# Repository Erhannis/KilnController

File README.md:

Kiln controller PCB, in KiCAD.  ESP32, controlled (potentially) over wifi.

# Instructions 
Comes with two thermocouple readers and controls three heating elements.  Attach thermocouples to appropriate points, attach three SSR-DA60 to HEAT1-HEAT3 and another to ALL_POWER, wire in 240V (see instructions on board), recommended don't attach USB while mains voltage is connected; the 5V sources might conflict - also just seems a little unsafe.  The board is shaped to match my Everheat Classic 1210 frontplate - hopefully it fits, haha.  You can reshape it if you want, or just run wires to your thermocouples and elements.  The Main TC is for inside the kiln (PIDKiln has a link to a sturdy thermocouple), the Aux TC is for the kiln outside surface (I think it's optional?).  I broke out all 6 unused GPIO pins.  See [code](#code) for firmware.

Warning: if any elements are active, all elements are live at >= 120V.  There's a blue LED that lights up when any element is active; watch out for the blue LED.  ALSO!  I hear that SSRs can fail closed, meaning the elements may stay live even once the blue LED turns off.  So...maybe just unplug the thing if you're gonna touch the coils.

# Code
See my fork of PIDKiln at https://github.com/erhannis/PIDKiln
Note that in order to flash the code, the board must be unpowered to start, you need to connect BOOT to GND, plug the board in via USB, and then you have a handful of seconds to initiate a data transfer at 115200 baud (either the main code flashing, or the "ESP32 Sketch Data Upload").  Try turning on Arduino IDE logs for compilation and upload, then copy the relevant upload command into the terminal, for timing.  Afterward, remove boot jumper and replug the board.

Disclaimer: I have no formal electronics training, and this thing connects to 240V, so like, maybe use this thing away from anything flammable, and on your own head be the results.  And DON'T TOUCH THE COILS WHILE IT'S HEATING!  Because they're live 240V, and also may be hot.

# Additional parts
Thermocouple: https://www.auberins.com/index.php?main_page=product_info&cPath=20_3&products_id=39
  (Also one of the cheap k-type thermocouples from amazon, for the case.  Though, see notes.)
Bus blocks: https://www.amazon.com/dp/B0B2L7QBVN
Heat sinks: https://www.amazon.com/dp/B08ZCYBPTV
SSRs: https://www.amazon.com/dp/B01MSTFKIP (60DA)
  Note that (according to tests) these start and stop conducting at zero volt crossings.  Also, they still let like 2mA through while open, which CAN yield high voltages.
  You might get away with lower amp ones.

# Notes
I picked the slightly more expensive thermocouple readers, which (supposedly) are more accurate and support multiple thermocouple types instead of just K - just in case that turns out to be useful.  If you're not using k-type, though, you'll probably need to tweak something in code to tell the controllers so.
I had trouble where at high temperatures, the readings on both thermocouples would go nuts.  This stopped happening after I hung the case thermocouple away from contact with anything else.  I am baffled as to how that could have happened.

MIT license.

-Erhannis

Btw, I have like 4 extra from the manufacturing batch if anybody want to buy one for like, I dunno, $100, say.  (You'll have to add the SSRs and bus terminals yourself, though.)  Getting 5 boards assembled from JLCPCB costs around $330 total.
(If you're up for soldering the ESP32 WROOM module yourself (difficult), you can use Economy mode instead of Standard and save like $100.)

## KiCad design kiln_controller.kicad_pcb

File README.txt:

Kiln controller PCB, in KiCAD.  ESP32, controlled (potentially) over wifi.

# Instructions
Comes with two thermocouple readers and controls three heating elements.  Attach thermocouples to appropriate points, attach three SSR-DA60 to HEAT1-HEAT3 and another to ALL_POWER, wire in 240V (see instructions on board), recommended don't attach USB while mains voltage is connected; the 5V sources might conflict - also just seems a little unsafe.  The board is shaped to match my Everheat Classic 1210 frontplate - hopefully it fits, haha.  You can reshape it if you want, or just run wires to your thermocouples and elements.  The Main TC is for inside the kiln (PIDKiln has a link to a sturdy thermocouple), the Aux TC is for the kiln outside surface (I think it's optional?).  I broke out all 6 unused GPIO pins.  See [code](#code) for firmware.

Warning: if any elements are active, all elements are live at >= 120V.  There's a blue LED that lights up when any element is active; watch out for the blue LED.  ALSO!  I hear that SSRs can fail closed, meaning the elements may stay live even once the blue LED turns off.  So...maybe just unplug the thing if you're gonna touch the coils.

# Code
See my fork of PIDKiln at https://github.com/erhannis/PIDKiln
Note that in order to flash the code, you need to pull BOOT to GND, plug the board in via USB, and then you have a handful of seconds to initiate a data transfer at 115200 baud (either the main code flashing, or the "ESP32 Sketch Data Upload").  Try turning on Arduino IDE logs for compilation and upload, then copy the relevant upload command into the terminal, for timing.  Afterward, remove boot jumper and replug the board.

Disclaimer: I have no formal electronics training, and this thing connects to 240V, so like, maybe use this thing away from anything flammable, and on your own head be the results.  And DON'T TOUCH THE COILS WHILE IT'S HEATING!  Because they're live 240V, and also may be hot.

# Notes
I picked the slightly more expensive thermocouple readers, which (supposedly) are more accurate and support multiple thermocouple types instead of just K - just in case that turns out to be useful.  If you're not using k-type, though, you'll probably need to tweak something in code to tell the controllers so.

MIT license.

-Erhannis

Btw, I have like 4 extra from the manufacturing batch if anybody want to buy one for like, I dunno, $100, say.  (You'll have to add the SSRs and bus terminals yourself, though.)  Getting 5 boards assembled from JLCPCB costs around $330 total.
(If you're up for soldering the ESP32 WROOM module yourself (difficult), you can use Economy mode instead of Standard and save like $100.)

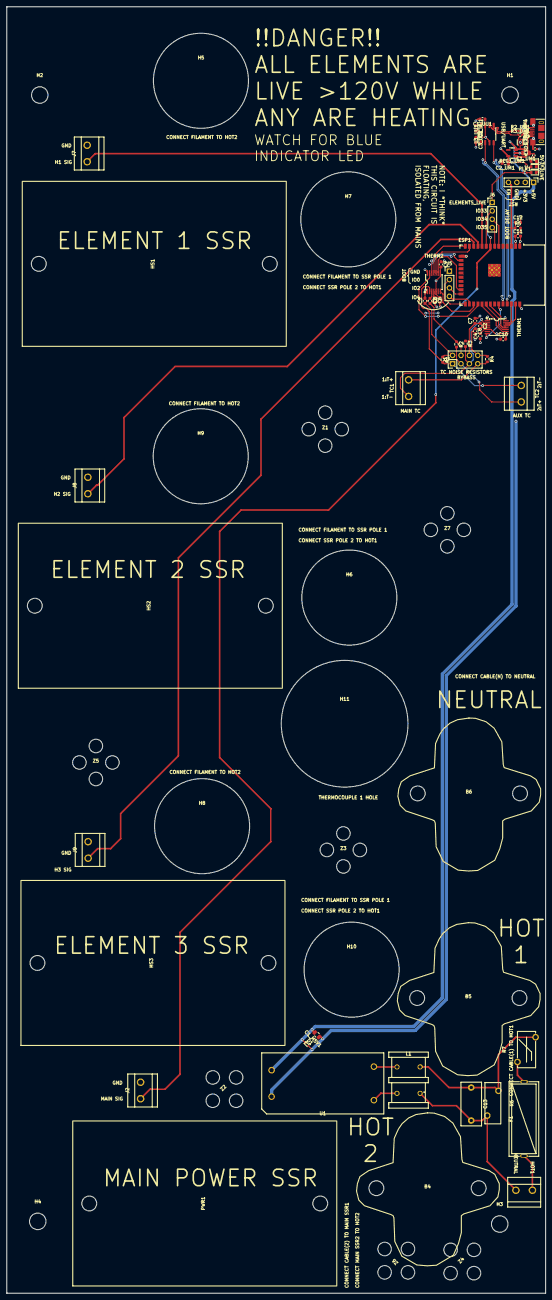
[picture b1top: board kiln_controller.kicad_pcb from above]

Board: 4 copper layers, 163.3 x 389.8 mm, 82 parts (0 on the bottom side), 51 nets.

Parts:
B4, B5, B6: bus_stud
C1, C2, C3, C4, C9, C10: 100nF; C_0603_1608Metric
C1_M5V1, C1_UM1, C2_UM1: 10uF; C_0805_2012Metric
C1_UU1, C2_UU1, C3_UU1, C12: 1uF; C_0603_1608Metric
C5, C6, C7, C8: 10nF; C_0603_1608Metric
C11: 22uF; C_0603_1608Metric
C13: 100nF/275V; C_Rect_L13.0mm_W6.0mm_P10.00mm_FKS3_FKP3_MKS4
D1: ESD9B5.0ST5G; D_SOD-923
D1_UM1: LED(R); LED_0603_1608Metric
D2_UM1: LED(G); LED_0603_1608Metric
ESD1_UM1: USBLC6-2P6; SOT-666
ESP1: ESP32-WROOM-32D
F1: Fuse transparent seat; FUSE-TH_L24.5-W9.8-P22.5
H1, H2, H3, H4: MountingHole; MountingHole_5mm
H5, H6, H7, H8, H9, H10: MountingHole; MountingHole_6mm
H11: MountingHole; MountingHole_6.5mm
HS1, HS2, HS3: SSR Heat Sink
J1: Conn_02x04_Row_Letter_First; PinHeader_2x04_P2.54mm_Vertical
J2, J7, J8, J9, J10: XY126V-5.0-2P; CONN-TH_XY126V-5.0-2P
J4, J5, J6: Conn_01x04_Pin; PinHeader_1x04_P2.54mm_Vertical
L1: UU9.8-20MH; FILTER-TH_4P-L17.0-W12.0-P7.00-D0.6-S8.00
PLED1: LED(B); LED_0603_1608Metric
PLR1: 330; R_0402_1005Metric
PWR1: SSR Heat Sink
R1, R2, R3, R4: 100Ω; R_0603_1608Metric
R1_UM1: 1M; R_0402_1005Metric
R2_UM1, R3_UM1: 27; R_0402_1005Metric
R4_UM1, R5_UM1: 330; R_0402_1005Metric
R5: 10k; R_0603_1608Metric
R6: 471KD10; RES-TH_L12.5-W4.8-P7.50-D1.2-S3.40
R7: 5D-9_C332361; RES-TH_L11.0-W5.5-P7.50-D0.8-S5.50
REG1_UM1: AP2112K-3.3; SOT-23-5
TC1, TC2: XY126V-5.0-2P; CONN-TH_XY126V-5.0-2P
THERM1, THERM2: MAX31856MUD+T; TSSOP-14_L5.0-W4.4-P0.65-LS6.4-BL
U1: EC03-S05_C2840800; PWRM-TH_EC03-S05
U1_UU1: HT42B534_8SOP; SOP-8_3.9x4.9mm_P1.27mm
USB1_UM1: USB_B_Micro; USB_Micro-B_XKB_U254-051T-4BH83-F1S
Z1, Z2, Z3, Z4, Z5, Z6, Z7: zip_tie_big

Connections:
+3V3: C1_UU1.1, C2_UM1.1, C3.2, C3_UU1.1, C4.2, C9.2, C10.2, C11.1, ESP1.2 (VDD), J4.2, R5.2, R5_UM1.1, REG1_UM1.5 (VOUT), THERM1.5 (AVDD), THERM1.8 (DVDD), THERM2.5 (AVDD), THERM2.8 (DVDD), U1_UU1.3 (VDDIO), U1_UU1.7 (VDD)
+5V: C1_M5V1.2, C1_UM1.1, D1.1 (A1), ESD1_UM1.5 (VBUS), J4.1, R4_UM1.1, REG1_UM1.1 (VIN), REG1_UM1.3 (EN), U1.5 (+Vo), USB1_UM1.1 (VBUS)
/EN: C12.1, ESP1.3 (EN), J4.4, R5.1
/USB Micro B/USB D+: R2_UM1.1, U1_UU1.5 (D+)
/USB Micro B/USB D-: R3_UM1.1, U1_UU1.6 (D-)
/USB-UART/RX: ESP1.35 (TXD0/IO1), U1_UU1.4 (RX)
/USB-UART/TX: ESP1.34 (RXD0/IO3), U1_UU1.2 (TX)
ALL_POWER: ESP1.8 (IO32), J2.1, J6.1, PLR1.1
GND: C1_M5V1.1, C1_UM1.2, C1_UU1.2, C2_UM1.2, C2_UU1.2, C3.1, C3_UU1.2, C4.1, C5.2, C6.2, C7.2, C8.2, C9.1, C10.1, C11.2, C12.2, D1.2 (A2), D1_UM1.1 (K), D2_UM1.1 (K), ESD1_UM1.2 (GND), ESP1.1 (GND), ESP1.15 (GND), ESP1.38 (GND), ESP1.39 (GND), J2.2, J4.3, J5.1, J7.2, J8.2, J9.2, PLED1.1 (K), R1_UM1.1, REG1_UM1.2 (GND), THERM1.1 (AGND), THERM1.14 (DGND), THERM2.1 (AGND), THERM2.14 (DGND), U1.3 (-Vo), U1_UU1.1 (GND), USB1_UM1.5 (GND)
HEAT1: ESP1.10 (IO25), J7.1
HEAT2: ESP1.11 (IO26), J8.1
HEAT3: ESP1.12 (IO27), J9.1
unnamed: C13.1, L1.4, R6.1, R7.2
unnamed: C13.2, J10.1, L1.1, R6.2
unnamed: D1_UM1.2 (A), R4_UM1.2
unnamed: D2_UM1.2 (A), R5_UM1.2
unnamed: ESP1.25 (IO0), J5.2
unnamed: ESP1.24 (IO2), J5.3
unnamed: ESP1.26 (IO4), J5.4
unnamed: ESP1.29 (IO5), THERM1.9 (~CS)
unnamed: ESP1.14 (IO12), THERM2.11 (SDO)
unnamed: ESP1.16 (IO13), THERM2.12 (SDI)
unnamed: ESP1.13 (IO14), THERM2.10 (SCK)
unnamed: ESP1.23 (IO15), THERM2.9 (~CS)
unnamed: ESP1.27 (IO16), THERM2.7 (~DRDY)
unnamed: ESP1.28 (IO17), THERM2.13 (~FAULT)
unnamed: ESP1.30 (IO18), THERM1.10 (SCK)
unnamed: ESP1.31 (IO19), THERM1.11 (SDO)
unnamed: ESP1.33 (IO21), THERM1.7 (~DRDY)
unnamed: ESP1.36 (IO22), THERM1.13 (~FAULT)
unnamed: ESP1.37 (IO23), THERM1.12 (SDI)
unnamed: ESP1.9 (IO33), J6.2
unnamed: ESP1.6 (IO34), J6.3
unnamed: ESP1.7 (IO35), J6.4
unnamed: F1.1, J10.2
unnamed: F1.2, R7.1
unnamed: J1.1, R1.2, TC2.1, THERM2.2 (BIAS)
unnamed: C1.1, C5.1, J1.2, R1.1, THERM2.3 (T-)
unnamed: J1.3, R2.2, TC2.2
unnamed: C1.2, C6.1, J1.4, R2.1, THERM2.4 (T+)
unnamed: J1.5, R3.2, TC1.1, THERM1.2 (BIAS)
unnamed: C2.1, C7.1, J1.6, R3.1, THERM1.3 (T-)
unnamed: J1.7, R4.2, TC1.2
unnamed: C2.2, C8.1, J1.8, R4.1, THERM1.4 (T+)
unnamed: PLED1.2 (A), PLR1.2
unnamed: L1.3, U1.1 (AC(L))
unnamed: L1.2, U1.2 (AC(N))
unnamed: C2_UU1.1, U1_UU1.8 (V33O)
unnamed: ESD1_UM1.1 (I/O1), ESD1_UM1.6 (I/O1), R2_UM1.2, USB1_UM1.3 (D+)
unnamed: ESD1_UM1.3 (I/O2), ESD1_UM1.4 (I/O2), R3_UM1.2, USB1_UM1.2 (D-)
unnamed: R1_UM1.2, USB1_UM1.6 (Shield)

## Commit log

2024-01-09 Kiln controller. Probably should have committed before now. Nearly done with the schematic.
2024-01-09 Added readme
2024-01-09 Comments etc. Also added mains power module.
2024-01-09 Disclaimer
2024-01-09 Working on pcb
2024-01-10 Added warning. Also added some footprints of larger hardware, and laid out the board shape.
2024-01-10 Board mostly laid out
2024-01-10 Comments
2024-01-11 Decided to add a safety relay. This meant swapping for smaller bus blocks.
2024-01-11 Nearing completion
2024-01-11 Tweaks and stuff. I think it's about ready?
2024-01-12 Ok, DRC passes (basically)
2024-01-12 Updated power module for filtering and tvs etc.
2024-01-12 Added blue danger LED. Passes ERC.
2024-01-12 Also passes DRC
2024-01-12 Added image and URL
2024-01-12 Added hash. I think it's time for production.
2024-01-12 Eh, the esp32 gnd pad vias were smaller than the jlcpcb default minimum
2024-01-12 hash
2024-01-12 Ahh, heck; I accidentally added an LED with only 1 in stock
2024-01-12 Oops, didn't hit save, I guess
2024-01-12 haaaaash
2024-01-12 Slight text tweak. Not significant enough to affect manufacturing. Also, order has been placed - I hope I haven't forgotten anything important.
2024-01-12 Tweaks or st
2024-03-30 Apparently I forgor commit readme changes
2024-03-30 Argh, I forgot to stage readme
2024-03-30 Update and rename README.txt to README.md
    Fixed the image
2024-03-30 Fixed source
